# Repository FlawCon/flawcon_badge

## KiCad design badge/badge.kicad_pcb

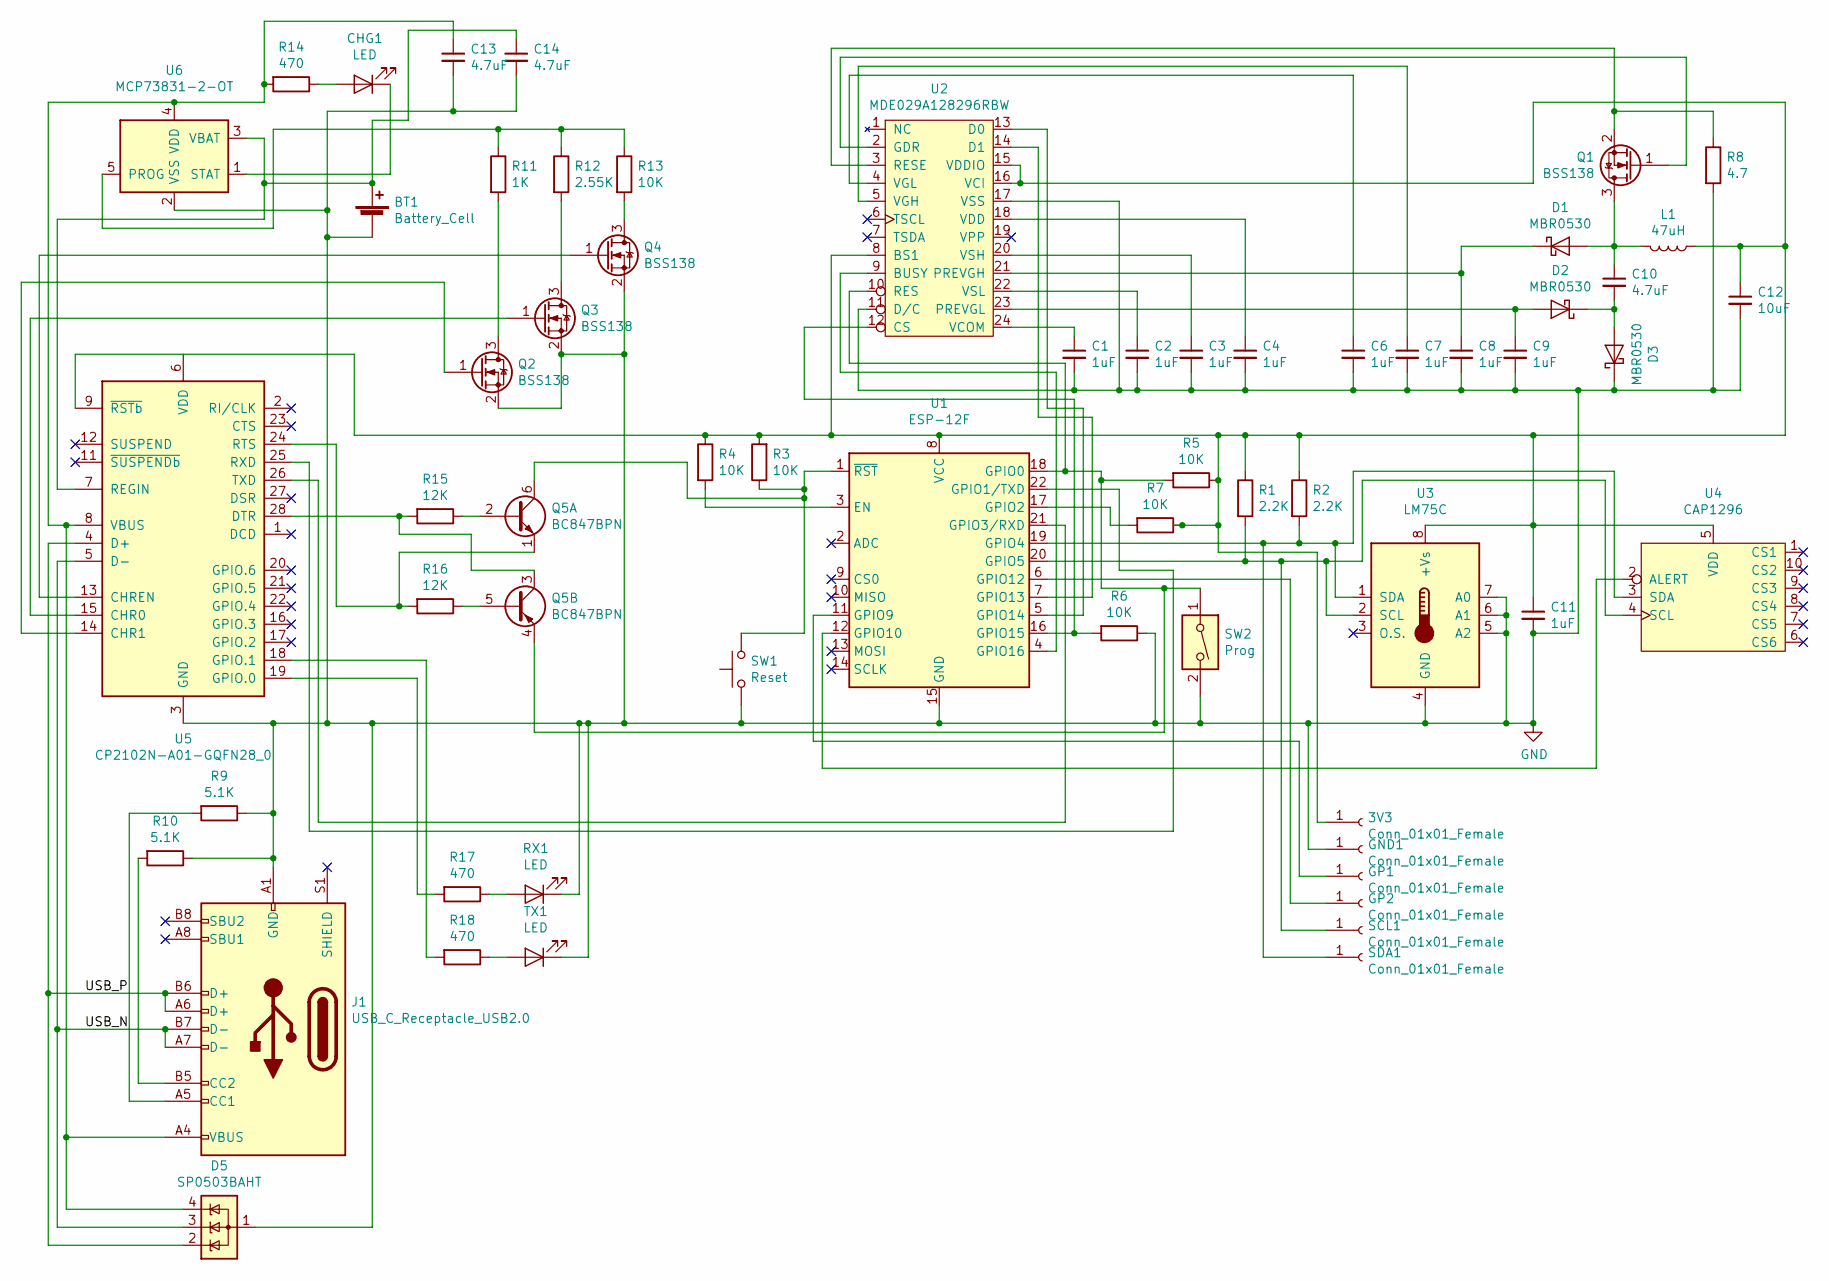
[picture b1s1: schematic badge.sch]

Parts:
3V3: Conn_01x01_Female; PinHeader_1x01_P1.00mm_Vertical
BT1: Battery_Cell; JST_XH_S02B-XH-A-1_1x02_P2.50mm_Horizontal
C1, C2, C3, C4, C6, C7, C8, C9, C11: 1uF; C_0805_2012Metric
C10, C13, C14: 4.7uF; C_0402_1005Metric
C12: 10uF; C_0805_2012Metric
CHG1: LED; LED_0603_1608Metric_Castellated
D1, D2, D3: MBR0530; D_SOD-123
D5: SP0503BAHT; SOT-143
GND1: Conn_01x01_Female; PinHeader_1x01_P1.00mm_Vertical
GP1, GP2: Conn_01x01_Female; PinHeader_1x01_P1.00mm_Vertical
J1: USB_C_Receptacle_USB2.0; USB_C_Receptacle_Amphenol_12401548E4-2A
L1: 47uH; L_6.3x6.3_H3
Q1, Q2, Q3, Q4: BSS138; SOT-23
Q5: BC847BPN; SOT-363_SC-70-6
R1, R2: 2.2K; R_0805_2012Metric
R3, R4, R5, R6, R7, R13: 10K; R_0402_1005Metric
R8: 4.7; R_0603_1608Metric
R9, R10: 5.1K; R_0603_1608Metric
R11: 1K; R_0402_1005Metric
R12: 2.55K; R_0805_2012Metric
R14, R17, R18: 470; R_1206_3216Metric
R15, R16: 12K; R_0402_1005Metric
RX1: LED; LED_0603_1608Metric_Castellated
SCL1: Conn_01x01_Female; PinHeader_1x01_P1.00mm_Vertical
SDA1: Conn_01x01_Female; PinHeader_1x01_P1.00mm_Vertical
SW1: Reset; SW_SPST_B3U-3000P
SW2: Prog; SW_SPDT_PCM12
TX1: LED; LED_0603_1608Metric_Castellated
U1: ESP-12F; ESP-12E
U2: MDE029A128296RBW; Hirose_FH12-24S-0.5SH_1x24-1MP_P0.50mm_Horizontal
U3: LM75C; SOIC-8_3.9x4.9mm_P1.27mm
U4: CAP1296; DFN-10-1EP_3x3mm_P0.5mm_EP1.75x2.7mm
U5: CP2102N-A01-GQFN28_0; QFN-28-1EP_5x5mm_P0.5mm_EP3.35x3.35mm
U6: MCP73831-2-OT; SOT-23-5

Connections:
/USB_N: D5.3 (K), J1.A7 (D-), J1.B7 (D-), U5.5 (D-)
/USB_P: D5.2 (K), J1.A6 (D+), J1.B6 (D+), U5.4 (D+)
GND: BT1.2 (-), C1.2, C2.2, C3.2, C4.2, C6.2, C7.2, C8.2, C9.2, C11.2, C12.2, C13.2, C14.2, D3.1 (K), D5.1 (A), GND1.1, J1.A1 (GND), J1.A12 (GND), J1.B1 (GND), J1.B12 (GND), Q2.2 (S), Q3.2 (S), Q4.2 (S), R6.1, R8.2, R9.1, R10.1, RX1.1 (K), SW1.1, SW2.2, TX1.1 (K), U1.15 (GND), U2.11 (D/C), U2.17 (VSS), U3.4 (GND), U3.5 (A2), U3.6 (A1), U3.7 (A0), U5.3 (GND), U6.2 (VSS); also elsewhere on the board
unnamed: 3V3.1, C11.1, C12.1, L1.1, R1.1, R2.1, R3.2, R4.1, R5.1, R7.1, U1.8 (VCC), U2.8 (BS1), U2.15 (VDDIO), U2.16 (VCI), U3.8 (+Vs), U4.5 (VDD), U5.9 (~RSTb)
unnamed: BT1.1 (+), C14.1, U5.7 (REGIN), U6.3 (VBAT)
unnamed: C1.1, U2.24 (VCOM)
unnamed: C2.1, U2.22 (VSL)
unnamed: C3.1, U2.20 (VSH)
unnamed: C4.1, U2.18 (VDD)
unnamed: C6.1, U2.4 (VGL)
unnamed: C7.1, U2.5 (VGH)
unnamed: C8.1, D1.1 (K), U2.21 (PREVGH)
unnamed: C9.1, D2.2 (A), U2.23 (PREVGL)
unnamed: C10.1, D1.2 (A), L1.2, Q1.3 (D)
unnamed: C10.2, D2.1 (K), D3.2 (A)
unnamed: C13.1, D5.4 (K), J1.A4 (VBUS), J1.A9 (VBUS), J1.B4 (VBUS), J1.B9 (VBUS), R14.2, U5.8 (VBUS), U6.4 (VDD)
unnamed: CHG1.1 (K), U6.1 (STAT)
unnamed: CHG1.2 (A), R14.1
unnamed: GP1.1, U1.11 (GPIO9)
unnamed: GP2.1, U1.6 (GPIO12)
unnamed: J1.A5 (CC1), R9.2
unnamed: J1.B5 (CC2), R10.2
unnamed: Q1.1 (G), U2.2 (GDR)
unnamed: Q1.2 (S), R8.1, U2.3 (RESE)
unnamed: Q2.1 (G), U5.14 (CHR1)
unnamed: Q2.3 (D), R11.2
unnamed: Q3.1 (G), U5.15 (CHR0)
unnamed: Q3.3 (D), R12.2
unnamed: Q4.1 (G), U5.13 (CHREN)
unnamed: Q4.3 (D), R13.2
unnamed: Q5.1 (E1), R16.2, U5.24 (RTS)
unnamed: Q5.2 (B1), R15.1
unnamed: Q5.3 (C2), R15.2, U5.28 (DTR)
unnamed: Q5.4 (E2), R5.2, SW2.1, U1.18 (GPIO0), U2.10 (RES)
unnamed: Q5.5 (B2), R16.1
unnamed: Q5.6 (C1), R3.1, SW1.2, U1.1 (~RST)
unnamed 43: R1.2, SCL1.1, U1.20 (GPIO5), U3.2 (SCL), U4.4 (SCL); also elsewhere on the board
unnamed 44: R2.2, SDA1.1, U1.19 (GPIO4), U3.1 (SDA), U4.3 (SDA); also elsewhere on the board
unnamed: R4.2, U1.3 (EN)
unnamed: R6.2, U1.16 (GPIO15), U2.12 (CS)
unnamed: R7.2, U1.17 (GPIO2)
unnamed: R11.1, R12.1, R13.1, U6.5 (PROG)
unnamed: R17.1, RX1.2 (A)
unnamed: R17.2, U5.19 (GPIO.0)
unnamed: R18.1, TX1.2 (A)
unnamed: R18.2, U5.18 (GPIO.1)
unnamed: U1.4 (GPIO16), U2.9 (BUSY)
unnamed: U1.5 (GPIO14), U2.13 (D0)
unnamed: U1.7 (GPIO13), U2.14 (D1)
unnamed: U1.12 (GPIO10), U4.2 (ALERT)
unnamed: U1.21 (GPIO3/RXD), U5.26 (TXD)
unnamed: U1.22 (GPIO1/TXD), U5.25 (RXD)

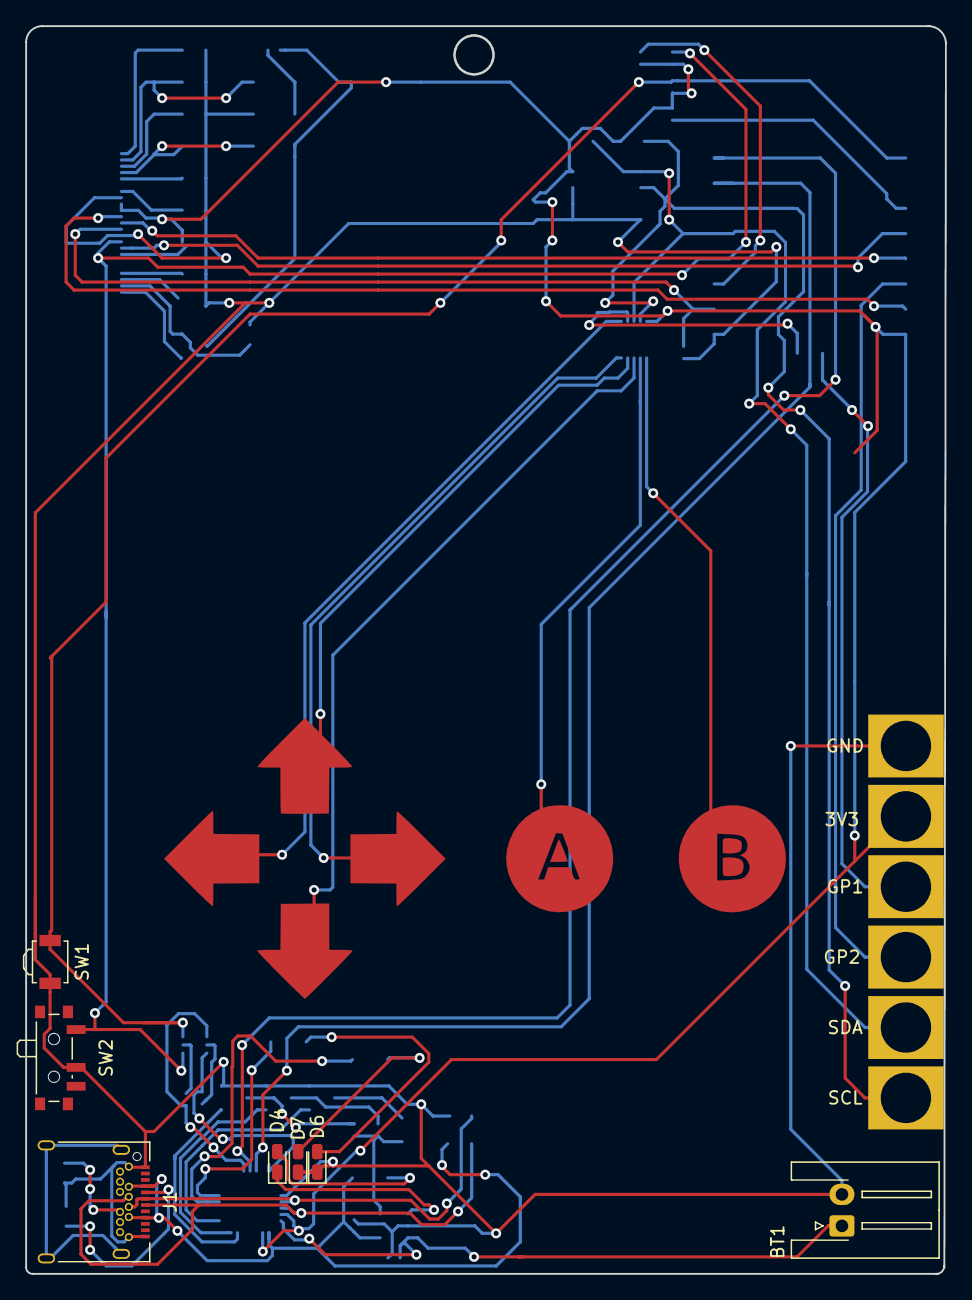
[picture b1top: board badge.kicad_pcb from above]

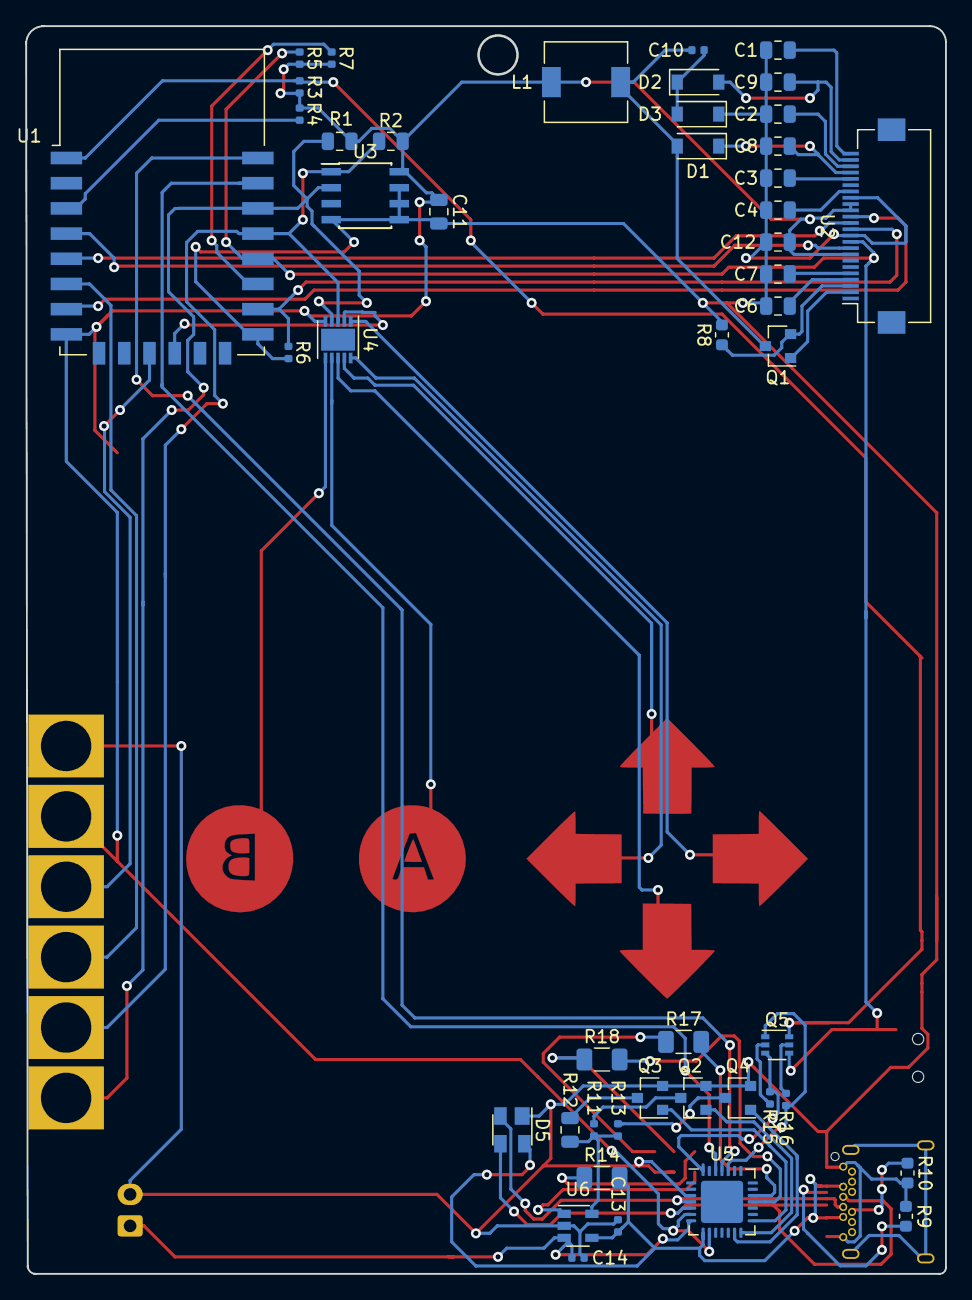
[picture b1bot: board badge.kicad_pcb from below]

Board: 2 copper layers, 73.0 x 99.0 mm, 60 parts (47 on the bottom side), 48 nets.

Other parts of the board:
D4, D6, D7: LED; LED_0603_1608Metric_Castellated
GND: Conn_01x01_Female; Banana_THT
SCL: Conn_01x01_Female; Banana_THT
SDA: Conn_01x01_Female; Banana_THT

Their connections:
GND: D6.1, D7.1, GND.1; also elsewhere on the board
unnamed 43: SCL.1; also elsewhere on the board
unnamed 44: SDA.1; also elsewhere on the board

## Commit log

2019-01-19 Updated badge footprint
2019-01-19 Start on firmware
2019-01-19 Micropython submodule
2019-01-19 Suff
2019-01-21 Start on EPD drivers
2019-01-21 Finish EPD driver
2019-01-21 Start on cap touch driver
2019-01-21 ADT driver
2019-01-21 Basic OS interface and test app
2019-01-21 C QR Code gen lib
2019-01-21 Fix lack of relative imports
2019-01-21 Typo
2019-01-22 Read temp into EPD display
2019-01-24 Buffer QR code input, and add 1 module border to matrix output
2019-01-24 gitignore
2019-01-24 .gitignore fix
2019-01-25 Setup app
2019-01-25 Improved speed on display write
2019-01-25 Minor changes to QR module
2019-01-25 WebREPL
2019-01-25 QR mod docs
